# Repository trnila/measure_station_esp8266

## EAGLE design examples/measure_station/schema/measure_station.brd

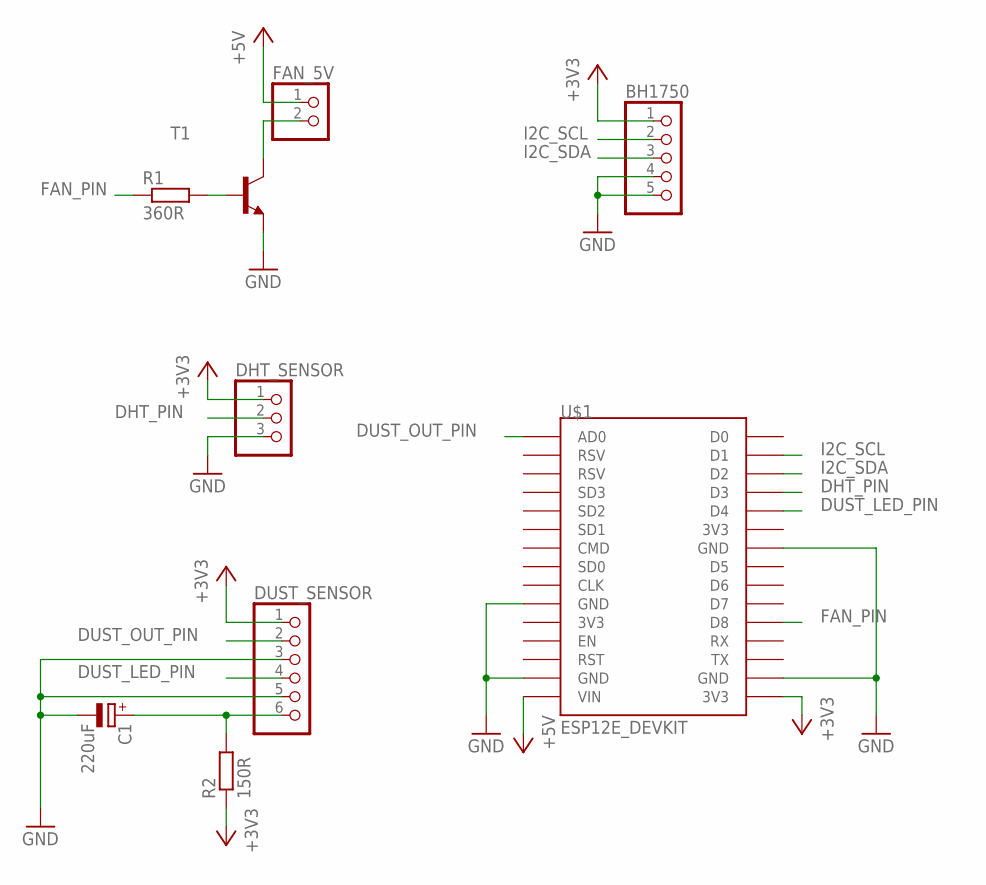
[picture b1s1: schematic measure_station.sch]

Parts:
BH1750: PINHD-1X5; 1X05
C1: 220uF; E2,5-5
DHT_SENSOR: PINHD-1X3; 1X03
DUST_SENSOR: PINHD-1X6; 1X06
FAN_5V: PINHD-1X2; 1X02
R1: 360R; 0204/7
R2: 150R; 0204/7
T1: MPS2222A-NPN-TO92-CBE; TO92-CBE
U$1: ESP12E_DEVKIT

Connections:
+3V3: BH1750.1, DHT_SENSOR.1, DUST_SENSOR.1, R2.1, U$1.3V3@2 (3V3)
+5V: FAN_5V.1, U$1.VIN
DHT_PIN: DHT_SENSOR.2, U$1.D3
DUST_LED_PIN: DUST_SENSOR.4, U$1.D4
DUST_OUT_PIN: DUST_SENSOR.2, U$1.AD0
FAN_PIN: R1.1, U$1.D8
GND: BH1750.4, BH1750.5, C1.-, DHT_SENSOR.3, DUST_SENSOR.3, DUST_SENSOR.5, T1.E, U$1.GND@0 (GND), U$1.GND@1 (GND), U$1.GND@2 (GND), U$1.GND@3 (GND)
I2C_SCL: BH1750.2, U$1.D1
I2C_SDA: BH1750.3, U$1.D2
unnamed: FAN_5V.2, T1.C
unnamed: R1.2, T1.B
unnamed: C1.+, DUST_SENSOR.6, R2.2

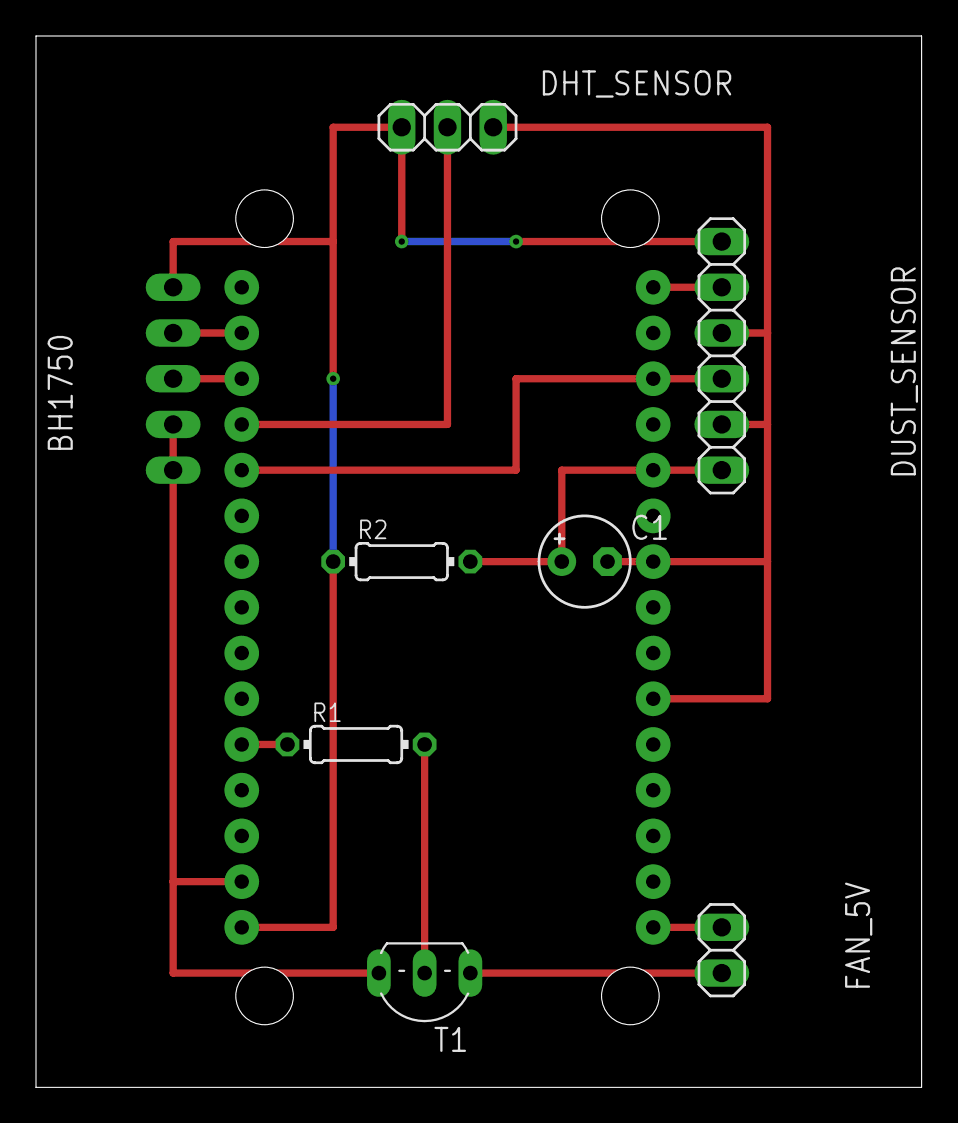
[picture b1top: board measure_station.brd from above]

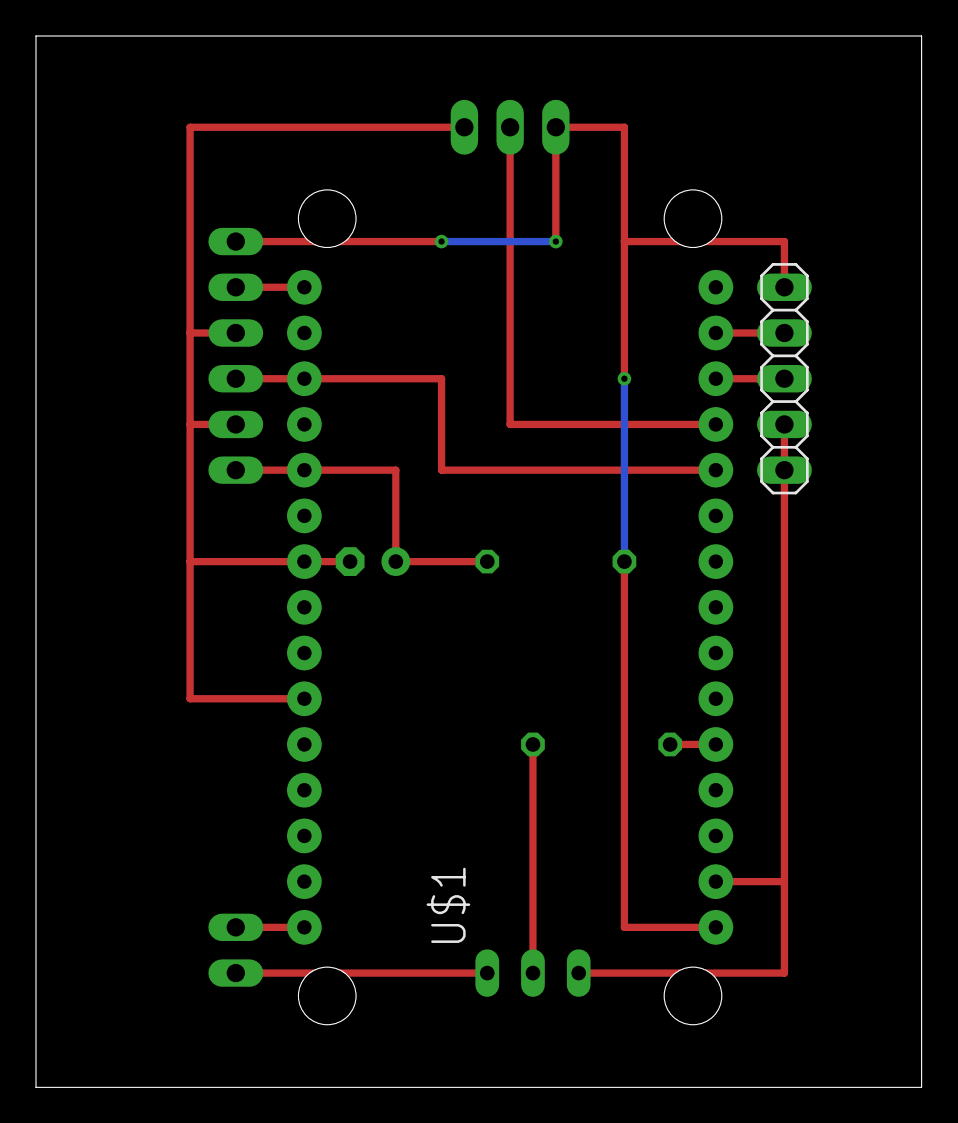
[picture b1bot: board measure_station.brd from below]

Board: 2 copper layers, 49.2 x 58.4 mm, 9 parts (2 on the bottom side), 12 nets.

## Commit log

2018-06-01 Initial commit for measure station
2018-06-02 measure_station: sending data via mqtt
2018-06-02 measure_station: refactored
2018-06-02 measure_station: mqtt base topic can be set in configuration
2018-06-02 Fan controller
2018-06-02 Added bh1750 lux sensor
2018-06-02 Added prototype schema
2018-06-02 Added eagle gitignore
2018-06-03 Debug macro
2018-06-03 Measure every minute
2018-06-03 added flash.sh
